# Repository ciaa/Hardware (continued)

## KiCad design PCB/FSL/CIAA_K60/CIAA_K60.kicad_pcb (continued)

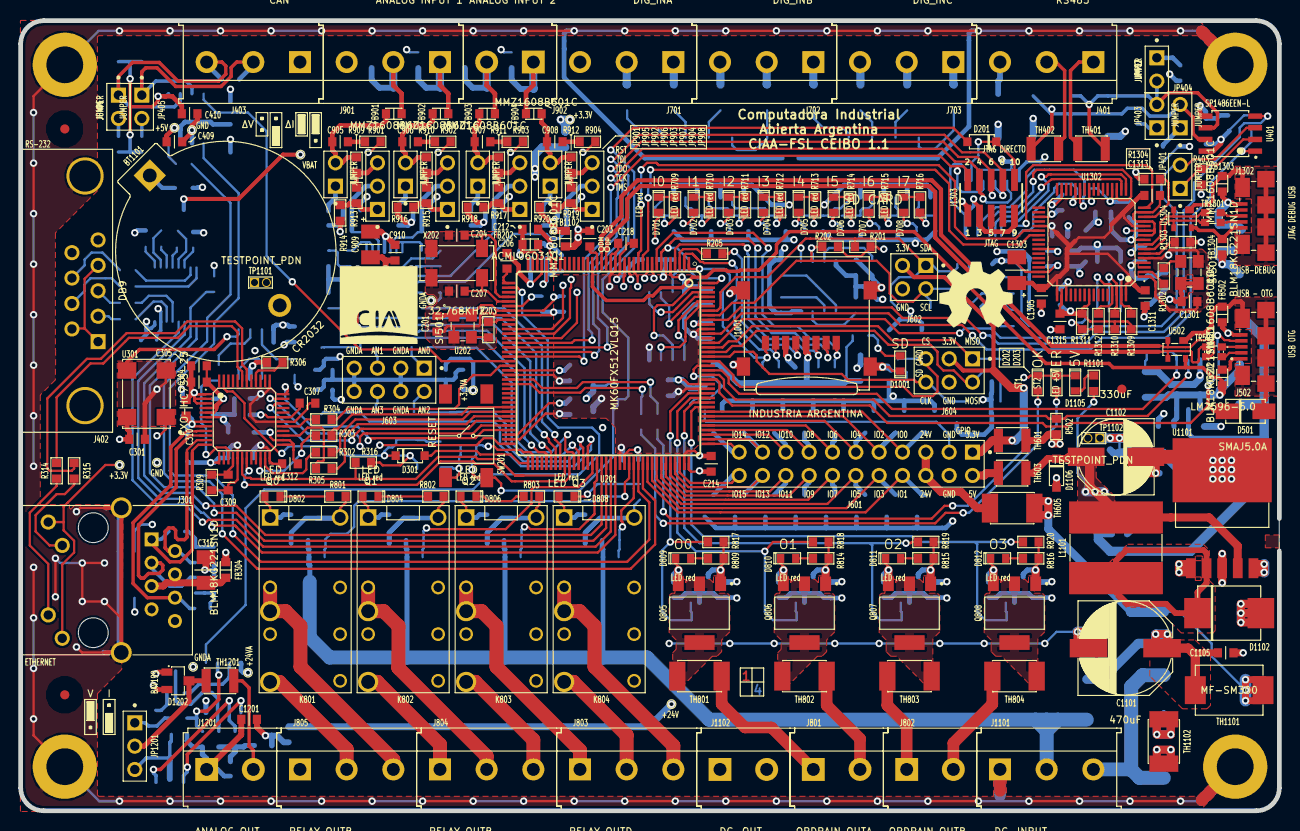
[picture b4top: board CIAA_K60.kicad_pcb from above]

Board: 4 copper layers, 137.0 x 86.0 mm, 467 parts (0 on the bottom side), 326 nets.

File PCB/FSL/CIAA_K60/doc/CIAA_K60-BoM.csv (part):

CIAA - PCB
10 sep 2014
CEIBO 1.0
CIAA - COMPUTADORA INDUSTRIAL ABIERTA ARGENTINA. Versión FSL Freescale K60
Autores: Ver 'doc/CHANGES.txt'      Licencia: Ver  'doc/LICENCIA_CIAA_FSL.txt'
Fecha de Generación: 19/09/2014-11:18:31

REF;VALUE;CANT;DESC;PN-DIGI-KEY;FAB;FOOT;DATA;URL
BT1101;CR2032;1;HOLDER BATTERY FOR 2032 CELL;BH32T-C-ND;MPD;2032batPTH;../datasheets/connectors/BH32T-C.pdf;http://search.digikey.com/scripts/DkSearch/dksus.dll?Detail&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
C201, C205, C206, C209, C210, C213, C214, C217, C218, C221, C223, C224, C227, C230, C302, C304, C305, C306, C307, C310, C312, C314, C315, C317, C402, C403, C404, C406, C407, C408, C409, C410, C501, C503, C801, C802, C803, C804, C910, C911, C912, C913, C914, C1001, C1002, C1003, C1005, C1104, C1106, C1201, C1301, C1302, C1305, C1306, C1307, C1311, C1312, C1313, C1314, C1315, C1316, C1317, C1318, C1319;100nF;64;CAP CER 0.1UF 16V 10% X7R 0603;399-1096-1-ND;Kemet;c_0603;../datasheets/passive/Capacitores/KEM_C1002_X7R_SMD.pdf;http://search.digikey.com/scripts/DkSearch/dksus.dll?Detail&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
C203;2.2uF;1;CAP CER 2.2UF 10V 10% X7R 0603;587-2983-1-ND;Taiyo Yuden;c_0603; ;http://search.digikey.com/scripts/DkSearch/dksus.dll?Detail&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
C204, C207;18pF;2;CAP CER 18PF 50V 5% NP0 0603;399-1052-1-ND;Kemet;c_0603; ;http://search.digikey.com/scripts/DkSearch/dksus.dll?Detail&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
C208, C212, C301, C1202;10nF;4;CAP CER 10000PF 50V 10% X7R 0603;399-1091-1-ND;Kemet;c_0603; ;http://search.digikey.com/scripts/DkSearch/dksus.dll?Detail&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
C231, C303, C401, C405, C909, C1004, C1103;10uF;7;CAP TANT 10UF 6.3V 10% 1206;399-10116-1-ND;Kemet;c_1206POL;../datasheets/passive/Capacitores/KEM_TC111_SPACE.pdf;http://search.digikey.com/scripts/DkSearch/dksus.dll?Detail&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
C308, C311, C313, C316;22uF;4;CAP TANT 22UF 6.3V 10% 1206;399-8279-1-ND;Kemet;c_1206POL; ;http://search.digikey.com/scripts/DkSearch/dksus.dll?Detail&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
C309;100pF;1;CAP CER 100PF 50V 10% X7R 0603;399-7824-1-ND;Kemet;c_0603; ;http://search.digikey.com/scripts/DkSearch/dksus.dll?Detail&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
C502, C1303, C1308, C1309, C1310;4,7uF;5;CAP TANT 4,7uF 6,3V 10% 1206 ;399-9717-1-ND;KEMET;c_1206POL; ;http://search.digikey.com/scripts/DkSearch/dksus.dll?Detail&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
C701, C702, C703, C704, C705, C706, C707, C708;1,5nF;8;CAP CER 1500PF 50V 10% X7R 0603;399-1084-1-ND;Kemet;c_0603; ;http://search.digikey.com/scripts/DkSearch/dksus.dll?Detail&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
C805, C806, C807, C808;1uF;4;CAP CER 1UF 16V 10% X7R 0603;399-7847-1-ND;Kemet;c_0603; ;http://search.digikey.com/scripts/DkSearch/dksus.dll?Detail&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
C901, C902, C903, C904;1nF;4;CAP CER 1000PF 50V 10% X7R 0603;399-1082-1-ND;Kemet;c_0603; ;http://search.digikey.com/scripts/DkSearch/dksus.dll?Detail&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
C905, C906, C907, C908;470pF;4;CAP CER 470PF 50V 10% X7R 0603;399-1075-1-ND;Kemet;c_0603; ;http://search.digikey.com/scripts/DkSearch/dksus.dll?Detail&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
C1101;470uF;1;CAP ALUM 470UF 35V 20% SMD;493-3961-1-ND;Nichicon;c_elec_10x13_5; ;http://search.digikey.com/scripts/DkSearch/dksus.dll?Detail&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
C1102;330uF;1;CAP ALUM 330UF 25V 20% SMD;493-9422-1-ND;Nichicon;c_elec_8x10; ;http://search.digikey.com/scripts/DkSearch/dksus.dll?Detail&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
C1105;100nF;1;CAP CER 0.1UF 50V 10% X7R 0603;1276-1936-1-ND;Samsung;c_0603; ;http://search.digikey.com/scripts/DkSearch/dksus.dll?Detail&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
D201, D301, D302, D801, D803, D805, D807;LL4148;7;DIODE SMALL SIG 100V 0.2A SOD80;LL4148FSCT-ND;Fairchild;SOD-123;../datasheets/passive/diode/LL4148.pdf;http://search.digikey.com/scripts/DkSearch/dksus.dll?Detail&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
D202, D1001;ST1, SD CARD;2;LED GRN WATER CLEAR 0603 SMD;1080-1399-1-ND;Everlight Electronics Co Ltd;LED-0603;../datasheets/passive/diode/ds300084.pdf;http://search.digikey.com/scripts/DkSearch/dksus.dll?Detail&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
D203, D701, D702, D703, D704, D705, D706, D707, D708, D802, D804, D806, D808, D809, D810, D811, D812, D1105;ST2, LED red, LED +5V;18;LED ALG RED WTR CLR 0603 SMD;1080-1400-1-ND;Everlight Electronics Co Ltd;LED-0603;../datasheets/passive/ds300084.pdf;http://search.digikey.com/scripts/DkSearch/dksus.dll?Detail&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
D401, D402, D403;P6SMB12CAT3G;3;TVS DIODE 10.2VWM 16.7VC SMB;P6SMB12CAT3GOSCT-ND;ON Semiconductor;DO-214AA_SMB;../datasheet/passive/diode/psd12c.pdf;http://search.digikey.com/scripts/DkSearch/dksus.dll?Detail&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
D404;PESD1CAN;1;TVS DIODE 24VWM 70VC SOT23;568-4032-1-ND;NXP Semiconductors;SOT-23;../datasheet/passive/diode/PESD1CAN.pdf;http://search.digikey.com/scripts/DkSearch/dksus.dll?Detail&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
D501;SMAJ5.0A;1;TVS DIODE 5VWM SMD;SMAJ5.0ABCT-ND;Bourns Inc.;DO-214AC_SMA;../datasheets/passive/protect/SMAJ.pdf;http://search.digikey.com/scripts/DkSearch/dksus.dll?Detail&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
D601, D602, D603, D604, D605, D606, D607, D609, D611, D612, D614, D615, D616, D617, D618, D619, D620, D621, D622, D624, D626, D627, D629, D630, D631, D632, D901, D902, D903, D904, D1201, D1202;BAV199;32;DIODE ARRAY 70V 215MA SOT23;BAV199LT1GOSCT-ND;ON Semiconductor;SOT-23;../datasheets/passive/protect/BAV199LT1-D.PDF;http://search.digikey.com/scripts/DkSearch/dksus.dll?Detail&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
D905, D906, D907, D908;P6SMB20CAT3G;4;TVS DIODE 17.1VWM 27.7VC SMB;P6SMB20CAT3GOSCT-ND;ON Semiconductor;DO-214AA_SMB;../ datasheets/passive/protect/P6SMB_Series.pdf;http://search.digikey.com/scripts/DkSearch/dksus.dll?Detail&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
D1101, D1109;MURS360;2;DIODE ULTRAFAST 600V 3A SMC;MURS360T3GOSCT-ND;ON Semiconductor;DO-214AB_SMC;../datasheet/passive/diode/MURS320T3-D.pdf;http://search.digikey.com/scripts/DkSearch/dksus.dll?Detail&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
D1102;MBRS540T3G;1;DIODE SCHOTTKY 40V 5A SMC;MBRS540T3GOSCT-ND;ON Semiconductor;DO-214AB_SMC;../datasheets/passive/diode/MBRS540T3-D.pdf;http://search.digikey.com/scripts/DkSearch/dksus.dll?Detail&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
D1103, D1104;MBRS130LT3G;2;DIODE SCHOTTKY 30V 2A SMB;MBRS130LT3GOSCT-ND;ON Semiconductor;DO-214AA_SMB;../datasheets/passive/diode/MBRS130LT3-D.pdf;http://search.digikey.com/scripts/DkSearch/dksus.dll?Detail&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
D1106;MMSZ5V6T1G;1;DIODE ZENER 5.6V 500MW SOD123;MMSZ5V6T1GOSCT-ND;ON Semiconductor;SOD-123;../datasheets/passive/diode/MMSZ2V4T1-D.pdf;http://search.digikey.com/scripts/DkSearch/dksus.dll?Detail&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
D1107;P6SMB33CA;1;TVS DIODE 28.2VWM 45.7VC SMB;P6SMB33CA-E3/52GICT-ND;Vishay Semiconductor Diodes Division;DO-214AA_SMB;../datasheets/passive/protect/P6SMB_Series.pdf;http://search.digikey.com/scripts/DkSearch/dksus.dll?Detail&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
D1108;BAT54C;1;DIODE SCHOTTKY 30V 200MA;BAT54FSCT-ND;Fairchild Semiconductor;SOT-23; ;http://search.digikey.com/scripts/DkSearch/dksus.dll?Detail&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
FB201, FB202;ACML0603101;2;FERRITE CHIP 100 OHM 200MA 0603;ACML-0603-101-TCT-ND;Abracon Corporation;fb_0603;../datasheets/passive/Ferrite/ACML-0603.pdf;http://search.digikey.com/scripts/DkSearch/dksus.dll?Detail&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
FB301, FB302, FB303, FB304;BK1608HS220-T;4;Ferrite Bead 22OHM 1500mA;Alternativo: MH1608-221YCT-ND;Taiyo Yuden;fb_0603;../datasheets/passive/Ferrite/BK1608HS220-T.pdf;http://search.digikey.com/scripts/DkSearch/dksus.dll?Detail&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 MH1608-221YCT-ND
FB402, FB403, FB404, FB405;BLM18BD470SN1;4;FERRITE CHIP 47 OHM 500MA 0603;490-5211-1-ND;Murata Electronics North America;fb_0603;../datasheet/passive/Ferrite/L0110S0100BLM18B.pdf;http://search.digikey.com/scripts/DkSearch/dksus.dll?Detail&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
FB501;BLM18KG221SN1D;1;FERRITE CHIP 220 OHM 2200MA 0603;490-5255-1-ND;MURATA;fb_0603;../datasheets/passive/Ferrite/L0110S0100BLM18K.pdf;http://search.digikey.com/scripts/DkSearch/dksus.dll?Detail&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
FB502, FB901, FB902, FB903, FB904, FB1101, FB1102, FB1201, FB1301, FB1302;MMZ1608B601C;10;FERRITE CHIP 600 OHM 500MA 0603;445-2166-1-ND;TDK Corporation;fb_0603;../datasheets/passive/Ferrite/E9412_MMZ.pdf;http://search.digikey.com/scripts/DkSearch/dksus.dll?Detail&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
FB1303, FB1304;BLM18BD331SN1D;2;FERRITE CHIP 330 OHM 200mA 0603;490-5251-1-ND;MURATA;fb_0603;../datasheets/passive/Ferrite/L0110S0100BLM18B.pdf;http://search.digikey.com/scripts/DkSearch/dksus.dll?Detail&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
J301;ETHERNET;1;CONN MAGJACK 1PORT 100 BASE-TX;553-1483-ND;Pulse;RJ45_Pulse_J403-A;../datasheets/connectors/J0011D01BNL.pdf;http://search.digikey.com/scripts/DkSearch/dksus.dll?Detail&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

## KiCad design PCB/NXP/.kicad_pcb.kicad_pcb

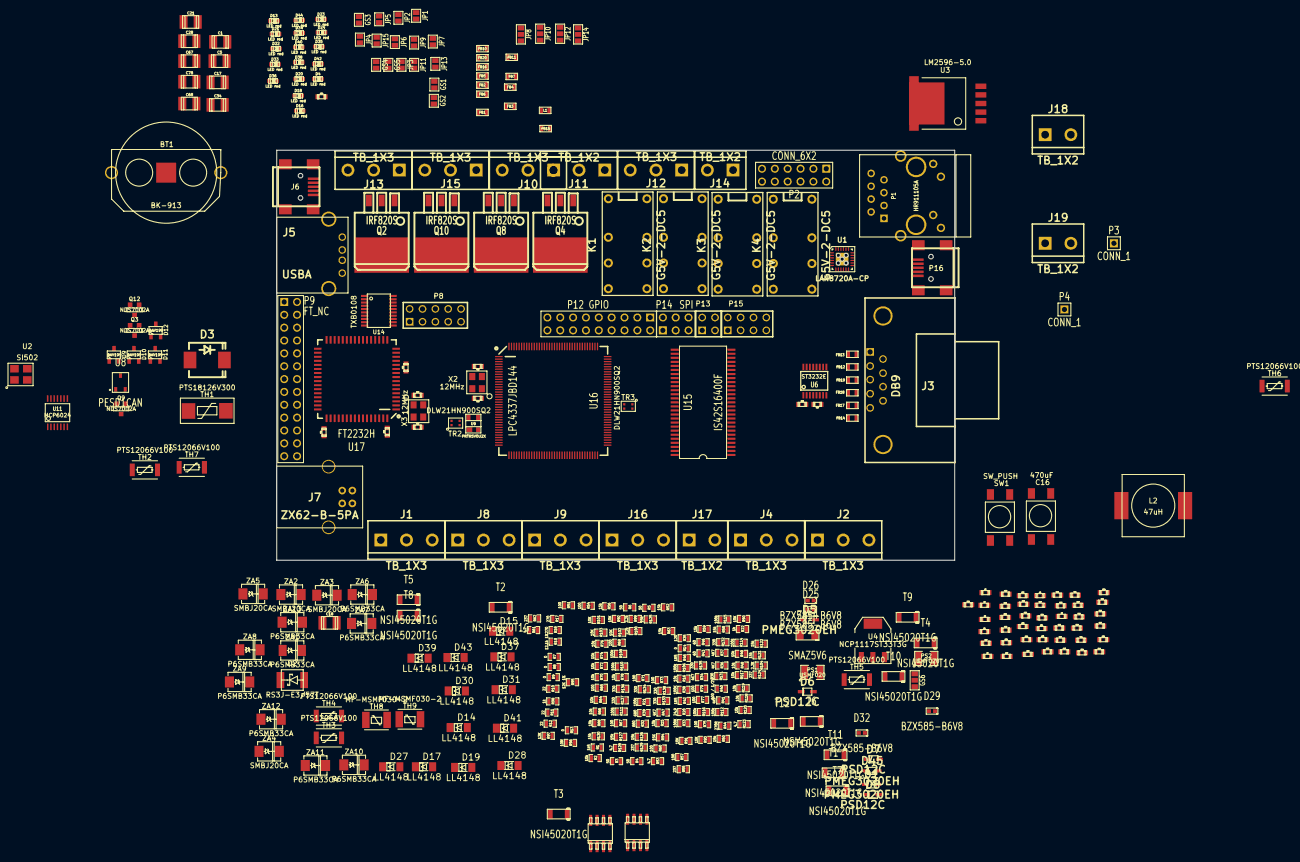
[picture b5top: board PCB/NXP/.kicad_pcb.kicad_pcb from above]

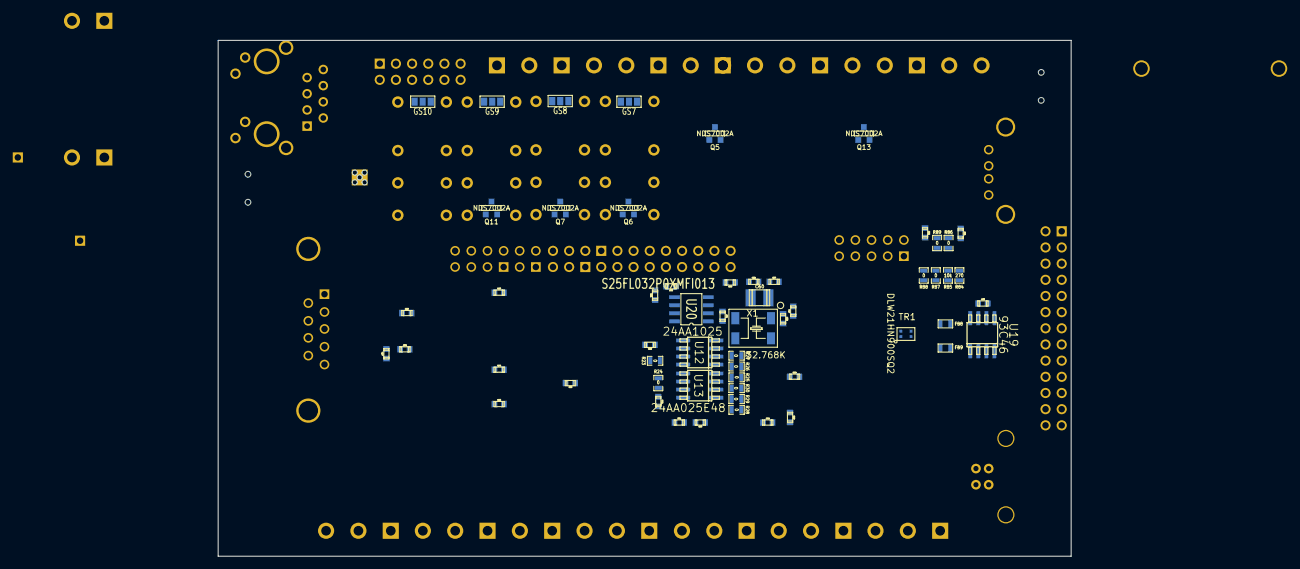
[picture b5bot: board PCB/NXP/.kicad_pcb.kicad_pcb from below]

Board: 4 copper layers, 134.0 x 81.0 mm, 420 parts (57 on the bottom side), 374 nets, no tracks yet.

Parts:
BT1: BK-913; BK-913-ND
C1, C5, C18, C34, C60, C68, C78: 10uF; c_1210
C2, C3, C4, C6, C7, C8, C9, C10, C15, C19, C20, C22, C23, C24, C25, C26, C27, C29, C30, C32, C33, C35, C37, C39, C41, C43, C45, C47, C48, C49, C50, C51, C52, C53, C54, C55, C56, C57, C58, C59, C61, C62, C63, C64, C65, C66, C69, C70, C71, C72, C73, C74, C75, C76, C77, C86, C87, C90: 100nF; c_0603
C11, C12, C13, C14: 18pF; c_0603
C16: 470uF; PUSH_SWITCH
C17: 330uF; c_1210
C21, C28: 10uF / 6V3; c_1210
C31: 10uF; c_0603
C36, C42, C91, C93: 1nF; c_0603
C38, C40, C44, C92: 470pF; c_0603
C67: 100nF; c_1210
C79, C81: 15p; c_0603
C80: 3.3uF; c_0603
C82, C83: 20p; c_0603
C84, C85: 22p; c_0603
D1, D5, D45: PMEG3020EH; SOD323
D2: RS3J-E3/57T; DO-214AB(SMC)
D3: B540C-13-F; Diode-SMC_Standard_RevA_26July2010
D4, D13, D16, D18, D20, D21, D22, D23, D24, D33, D34, D35, D36, D38, D40, D42, D44: LED red; LED-0603
D6, D7, D8: PSD12C; SOD323
D9, D10, D11, D12: BAV199; SOT23-DIODE
D14, D15, D17, D19, D27, D28, D30, D31, D37, D39, D41, D43: LL4148; MiniMelf
D25, D26, D29, D32: BZX585-B6V8; SOD523
FB1, FB2, FB3, FB4, FB5, FB6, FB8, FB9, FB10, FB20: MMZ1608B601C; SM0603
FB7, FB11, FB14, FB15, FB16: BLM18KG221SN1; SM0603
FB12, FB13, FB17, FB18, FB19: BLM18BD470SN1; SM0603
GS1, GS2, GS3, GS4, GS5: GS2
GS6, GS7, GS8, GS9, GS10: GS3
J1, J2, J4, J8, J9, J10, J12, J13, J15, J16: TB_1X3; bornier3
J3: DB9; DB9FC
J5: USBA; USB_A
J6: ZX62-AB-5PA; USB_MINI_B
J7: ZX62-B-5PA; USB_B
J11: TB_1X2; bornier3
J14, J17, J18, J19: TB_1X2; bornier2
JP1, JP2, JP3, JP4, JP5, JP6: JUMPER-2; GS2
JP7, JP9, JP11, JP13: JUMPER; GS2
JP8, JP10, JP12, JP14: JUMPER3; GS3
JP15: ISP; GS2
K1, K2, K3, K4: G5V-2-DC5; G5V-2
L1: BK1608HS220-T; SM0603
L2: 47uH; SMT power inductors
P1: HR911105A; RJ45_Pulse_J403-A
P2: CONN_6X2; PIN_ARRAY_6X2
P3, P4: CONN_1; PIN_ARRAY_1X1
P8: Cortex-Debug; PIN_ARRAY_5x2
P9: FT_NC; PIN_ARRAY_13X2
P12: GPIO; PIN_ARRAY_9X2
P13: I2C; PIN_ARRAY_2X2
P14: SPI; PIN_ARRAY_3X2
P15: Analog; pin_array_4x2
P16: ZX62-B-5PA; USB_MINI_B
PS1, PS2: USMF020; SM1210
Q2, Q4, Q8, Q10: IRF820S; TO263
Q3, Q5, Q6, Q7, Q9, Q11, Q12, Q13: NDS7002A; SOT23GDS
R1: 1k5; SM0603_Resistor
R2, R15, R16, R48, R49, R64, R66, R68, R70, R72, R74, R76, R78, R85, R117, R118, R119, R120: 10k; SM0603_Resistor
R3, R4, R5, R6: 50; SM0603_Resistor
R7, R8, R9, R13, R14, R23, R24, R25, R26, R27, R28, R29, R30, R86, R87, R88, R89: 0; SM0603_Resistor
R10, R11, R12: 22; SM0603_Resistor
R17, R18, R84: 270; SM0603_Resistor
R19: 12.1k 1%; SM0603_Resistor
R20: 24.9; SM0603_Resistor
R21, R106, R108, R110, R111, R112, R114, R115, R116: 100k; SM0603_Resistor
R22, R98: 1k; SM0603_Resistor
R32, R39: 680; SM0603_Resistor
R33, R38: 100K; SM0603_Resistor
R34, R36, R37, R41, R47: 4K7; SM0603_Resistor
R35: 120; SM0603_Resistor
R40: 100 / 1/2W; SM0603_Resistor
R42, R45: 1K5; SM0603_Resistor
R43, R46: 60; SM0603_Resistor
R44: 270R; SM0603_Resistor
R50, R52, R56, R58, R59, R63, R121, R122, R125, R126, R127, R130: 15k; SM0603_Resistor
R51, R54, R57, R60, R65, R67, R69, R71, R73, R75, R77, R79: 100; SM0603_Resistor
R53, R61, R123, R128: 4.7; SM0603_Resistor
R55, R62, R124, R129: 237; SM0603_Resistor
R90, R91, R92, R101, R102, R103: 10K; SM0603_Resistor
R93, R94: 15K; SM0603_Resistor
R95: 12K 1%; SM0603_Resistor
R96: 10M; SM0603_Resistor
R97: 12K; SM0603_Resistor
R99, R100: 2.2k; SM0603_Resistor
R104: 2.2K; SM0603_Resistor
R131, R132, R133, R134, R135, R136, R137, R138: 330; SM0603_Resistor
SW1: SW_PUSH; PUSH_SWITCH
T1, T2, T3, T4, T5, T6, T7, T8, T9, T10, T11, T12: NSI45020T1G; SOD123
TH1: PTS18126V300; MF-SM030
TH2, TH3, TH4, TH5, TH6, TH7: PTS12066V100; MF-USMF
TH8, TH9: MF-MSMF030-2; MF-MSMF
TR1, TR2, TR3: DLW21HN900SQ2; SRF2012
U1: LAN8720A-CP; QFN24
U2: SI502; 4SMD
U3: LM2596-5.0; D2PACK5-LM2596
U4: NCP1117ST33T3G; SOT223
U6: ST3232E; TSSOP16
U7: TJA1040; -SOIC8
U8: PESD1CAN; SOT23-3
U9: PRTR5V0U2X; sot143B
U10: MIC2025-2YM; -SOIC8
U11: MCP6024; TSSOP14
U12: 24AA1025; -SOIC8
U13: 24AA025E48; -SOIC8
U14: TXB0108; tssop-20
U15: IS42S16400F; TSOP54-M08-T2
U16: LPC4337JBD144; LQFP144-M05
U17: FT2232H; LQFP64-M08
U19: 93C46; -SOIC8
U20: S25FL032P0XMFI013; SO8
X1: 32.768K; 4SOJ
X2, X3: 12MHz; FA238V-XTAL
ZA1: P6SMB33CA; DO-214AC(SMA)
ZA2, ZA3, ZA4, ZA5: SMBJ20CA; DO-214AA(SMB)
ZA6, ZA7, ZA8, ZA9, ZA10, ZA11, ZA12, ZA13: P6SMB33CA; DO-214AA(SMB)
ZA14: SMAZ5V6; SOD123F

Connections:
+3.3V: C4.1, C5.1, C6.1, C15.1, C18.1, C19.1, C20.1, C21.2, C22.1, C23.1, C45.1, C47.2, C48.2, C49.2, C50.2, C51.2, C52.2, C53.2, C54.2, C55.2, C56.2, C57.2, C58.2, C61.2, C62.2, C63.1, C64.1, C65.1, C66.1, C73.1, C74.1, C75.1, C76.1, C90.1, D8.1, FB6.1, FB8.2, FB9.2, L1.1, P8.1, R1.1, R2.1, R15.1, R16.1, R18.1, R21.2, R27.1, R28.1, R32.1, R33.1, R34.1, R49.1, R64.2, R66.2, R68.2, R70.2, R72.2, R74.2, R76.2, R78.2, R90.2, R91.2, R92.2, R98.1, R99.1, R100.1, R101.1, R102.1, R103.1, R106.1, R108.1, R110.1, R114.1, TH8.1, U1.9, U2.4, U4.2, U6.16, U12.8, U13.8, U14.2, U14.19, U15.1, U15.3, U15.9, U15.14, U15.27, U15.43, U15.49, U16.5, U16.25, U16.36, U16.41, U16.59, U16.71, U16.77, U16.94, U16.107, U16.111, U16.131, U16.141, U17.20, U17.31, U17.42, U17.50, U17.56, U19.6, U19.8, U20.8
+3.3VADC: C34.1, C35.1, C59.1, C60.1, C86.1, C87.1, D9.3, D10.3, D11.3, D12.3, FB6.2, U11.4, U16.16, U16.17, U16.137
+5V: C17.1, C28.2, C29.2, C33.1, D1.2, D5.2, D27.2, D28.2, D30.2, D31.2, D45.2, K1.8, K2.8, K3.8, K4.8, L2.2, R22.1, R133.2, R134.2, R136.2, R137.2, TH9.2, U3.4, U4.3, U7.3, U10.7, ZA14.1
+24V: D2.2, T9.2, T10.2, T11.2, T12.2, TH1.1, TH2.1, TH3.2
/CPU/AIN0: C37.1, R51.2, U16.2
/CPU/AIN1: C39.1, R54.2, U16.143
/CPU/AIN2: C41.1, R57.2, U16.139
/CPU/AIN3: C43.1, R60.2, U16.138
/CPU/AUX_CLK: P12.14, U16.99
/CPU/CAN_RD: R44.1, U16.114
/CPU/CAN_TD: U7.1, U16.116
/CPU/DIN0: R64.1, U16.1
/CPU/DIN1: R66.1, U16.3
/CPU/DIN2: R68.1, U16.8
/CPU/DIN3: R70.1, U16.7
/CPU/DIN4: R72.1, U16.117
/CPU/DIN5: R74.1, U16.132
/CPU/DIN6: R76.1, U16.133
/CPU/DIN7: R78.1, U16.134
/CPU/DOUT0: Q6.G, R111.1, U16.9
/CPU/DOUT1: Q7.G, R112.1, U16.10
/CPU/DOUT2: Q11.G, R115.1, U16.11
/CPU/DOUT3: Q12.G, R116.1, U16.81
/CPU/DOUT4: Q3.G, R106.2, U16.15
/CPU/DOUT5: Q5.G, R108.2, U16.33
/CPU/DOUT6: Q9.G, R110.2, U16.35
/CPU/DOUT7: Q13.G, R114.2, U16.48
/CPU/EECLK: R102.2, U17.62, U19.2
/CPU/EECS: R103.2, U17.63, U19.1
/CPU/EEDATA: R104.1, U17.61, U19.3
/CPU/EMA_A1: U15.24, U16.104
/CPU/EMA_A2: U15.25, U16.105
/CPU/EMA_A6: U15.31, U16.42
/CPU/EMC_A0: U15.23, U16.102
/CPU/EMC_A3: U15.26, U16.106
/CPU/EMC_A4: U15.29, U16.108
/CPU/EMC_A5: U15.30, U16.38
/CPU/EMC_A7: U15.32, U16.43
/CPU/EMC_A8: U15.33, U16.98
/CPU/EMC_A9: JP15.2, U15.34, U16.96
/CPU/EMC_A10: U15.22, U16.95
/CPU/EMC_A11: U15.35, U16.84
/CPU/EMC_A13: U15.20, U16.75
/CPU/EMC_A14: U15.21, U16.86
/CPU/EMC_CAS: U15.17, U16.80
/CPU/EMC_CKE: U15.37, U16.101
/CPU/EMC_CLK0: U15.38, U16.45
/CPU/EMC_D0: U15.2, U16.50
/CPU/EMC_D1: U15.4, U16.51
/CPU/EMC_D2: U15.5, U16.52
/CPU/EMC_D3: U15.7, U16.53
/CPU/EMC_D4: U15.8, U16.55
/CPU/EMC_D5: U15.10, U16.56
/CPU/EMC_D6: U15.11, U16.60
/CPU/EMC_D7: U15.13, U16.61
/CPU/EMC_D8: U15.42, U16.57
/CPU/EMC_D9: U15.44, U16.58
/CPU/EMC_D10: U15.45, U16.63
/CPU/EMC_D11: U15.47, U16.65
/CPU/EMC_D12: U15.48, U16.37
/CPU/EMC_D13: U15.50, U16.39
/CPU/EMC_D14: U15.51, U16.46
/CPU/EMC_D15: U15.53, U16.54
/CPU/EMC_DYCS: U15.19, U16.97
/CPU/EMC_LDQM: U15.15, U16.103
/CPU/EMC_RAS: U15.18, U16.82
/CPU/EMC_UDQM: U15.39, U16.100
/CPU/EMC_WE: U15.16, U16.49
/CPU/ENET_CRS_DV: R12.1, U16.64
/CPU/ENET_MDC: R14.1, U16.140
/CPU/ENET_MDIO: R13.1, U16.66
/CPU/ENET_REF_CLK: R20.2, U1.5, U16.68
/CPU/ENET_RXD0: R10.1, U16.62
/CPU/ENET_RXD1: R11.1, U16.32
/CPU/ENET_TXD0: R7.1, U16.67
/CPU/ENET_TXD1: R8.1, U16.70
/CPU/ENET_TX_EN: R9.1, U16.34
/CPU/FT_OE: R84.2, U17.28
/CPU/FT_RST: U14.7, U17.27
/CPU/FT_TCK: U14.1, U17.16
/CPU/FT_TDI: U14.3, U17.17
/CPU/FT_TDO: U14.4, U17.18
/CPU/FT_TMS: U14.5, U17.19
/CPU/FT_TRST: U14.6, U17.26
/CPU/FT_XTIN: C84.2, U17.2, X3.2
/CPU/FT_XTOUT: C85.2, U17.3, X3.1
/CPU/GPIO0: GS6.3, P12.5, U16.74
/CPU/GPIO1: GS1.1, P12.6, U16.91
/CPU/GPIO2: GS2.1, P12.7, U16.110
/CPU/GPIO3: GS3.1, P12.8, P14.5, U16.85
/CPU/I2C_SCL: P13.2, R99.2, U12.6, U13.6, U16.92
/CPU/I2C_SDA: P13.1, R100.2, U12.5, U13.5, U16.93
/CPU/RS232_RXD: U6.12, U16.88
/CPU/RS232_TXD: U6.11, U16.87
/CPU/RS485_DIR: JP3.1, R37.1, U16.78
/CPU/RS485_TXD: R34.2, U16.69
/CPU/RTCX1: C81.2, U16.125, X1.2
/CPU/RTCX2: C79.2, U16.126, X1.1
/CPU/SPIFI_CS: U16.124, U20.1
/CPU/SPIFI_IO2: U16.121, U20.3
/CPU/SPIFI_IO3: U16.119, U20.7
/CPU/SPIFI_MISO: U16.122, U20.2
/CPU/SPIFI_MOSI: U16.123, U20.5
/CPU/SPI_MISO: P14.1, U16.44
/CPU/SPI_MOSI: P14.2, U16.47
/CPU/SPI_SCK: P14.6, U16.120
/CPU/TCK: P8.4, U14.20, U16.27
/CPU/TDI: P8.8, U14.18, U16.26
/CPU/TDO: P8.6, U14.17, U16.31
/CPU/TMS: P8.2, U14.16, U16.30
/CPU/U2_RXD: U16.115, U17.38
/CPU/U2_TXD: U16.113, U17.39
/CPU/USB_AUX_DM: TR3.3, U16.90
/CPU/USB_AUX_DP: TR3.2, U16.89
/CPU/USB_DEBUG_VBUS: D1.1, FB11.1
/CPU/USB_DM: R94.1, TR2.2, U9.2, U16.20
/CPU/USB_DP: R93.1, TR2.3, U9.3, U16.18
/CPU/USB_ID: J6.4, U16.22
/CPU/USB_JTAG_1.8V: C70.1, C71.1, C72.1, C80.1, U17.12, U17.37, U17.49, U17.64
/CPU/USB_JTAG_DM: TR1.2, U17.7
/CPU/USB_JTAG_DP: TR1.3, U17.8
/CPU/USB_VBUS: C31.1, C32.1, D5.1, FB15.2, U9.4, U10.6, U10.8, U16.21
/CPU/XTAL1: C82.2, R96.2, U16.12, X2.2
/CPU/XTAL2: C83.2, R96.1, U16.13, X2.1
/CPU/nTRST: R92.1, U16.29
/Entradas Digitales/COM: J9.3, ZA6.1, ZA7.1, ZA8.1, ZA9.1, ZA10.1, ZA11.1, ZA12.1, ZA13.1
/Entradas Digitales/IN0: J1.1, R65.1
/Entradas Digitales/IN1: J1.2, R67.1
/Entradas Digitales/IN2: J1.3, R69.1
/Entradas Digitales/IN3: J8.1, R71.1
/Entradas Digitales/IN4: J8.2, R73.1
/Entradas Digitales/IN5: J8.3, R75.1
/Entradas Digitales/IN6: J9.1, R77.1
/Entradas Digitales/IN7: J9.2, R79.1
/Ethernet/LED_100M: P1.11, R16.2, U1.2
/Ethernet/LED_LINK: P1.9, U1.3
/Ethernet/PHY_nRESET: GS6.2, U1.15
/GPIO/AN0: R117.1, U16.6
/GPIO/AN1: R119.1, U16.144
/GPIO/AN2: R118.1, U16.142
/GPIO/AN3: R120.1, U16.136
/GPIO/GPIO4: P12.9, U16.73
/GPIO/GPIO5: P12.10, U16.112
/GPIO/GPIO6: P12.11, U16.14
/GPIO/GPIO7: GS4.1, P12.12, U16.79
/GPIO/GPIO8: GS5.1, P12.13, U16.83
/GPIO/GPIO10: P12.15, U16.129
/GPIO/GPIO11: P12.16, U16.130
/GPIO/GPIO12: C69.1, GS6.1, P8.10, P12.17, R90.1, SW1.2, U16.128
/GPIO/USB_VBUS: D45.1, FB16.2
/GPIO/USR_3.3V: P12.1, P13.3, P14.3, TH8.2
/GPIO/USR_5V: P12.2, TH9.1
/Memorias NV/SPIFI_CLK: U16.118, U20.6
/RS485_RS232_CAN/CAN_H: J4.1, R42.2, R43.1, U7.7, U8.2
/RS485_RS232_CAN/CAN_L: J4.2, R45.1, R46.1, U7.6, U8.1
/RS485_RS232_CAN/CAN_STB: GS1.2, R47.2, U7.8
/RS485_RS232_CAN/RS232_CTS: GS3.2, U6.9
/RS485_RS232_CAN/RS232_RTS: GS2.2, R41.1, U6.10
/Salidas Digitales/NO1A: GS7.3, K1.16
/Salidas Digitales/NO1B: K1.1, P2.5
/Salidas Digitales/NO2A: GS8.3, K2.16
/Salidas Digitales/NO2B: K2.1, P2.11
/Salidas Digitales/NO3A: GS9.3, K3.16
/Salidas Digitales/NO3B: K3.1, P2.6
/Salidas Digitales/NO4A: GS10.3, K4.16
/Salidas Digitales/NO4B: K4.1, P2.12
/USB OTG/USB0_PPWR: GS4.2, R48.2, U10.1
/USB OTG/USB0_PWR_FAULT: GS5.2, R49.2, U10.2
GND: BT1.2, C1.2, C2.2, C3.2, C4.2, C5.2, C6.2, C7.2, C8.2, C9.2, C10.2, C11.2, C12.2, C13.2, C14.2, C15.2, C16.2, C17.2, C18.2, C19.2, C20.2, C21.1, C22.2, C23.2, C25.2, C27.2, C28.1, C29.1, C30.2, C31.2, C32.2, C33.2, C45.2, C47.1, C48.1, C49.1, C50.1, C51.1, C52.1, C53.1, C54.1, C55.1, C56.1, C57.1, C58.1, C61.1, C62.1, C63.2, C64.2, C65.2, C66.2, C67.2, C68.2, C69.2, C70.2, C71.2, C72.2, C73.2, C74.2, C75.2, C76.2, C77.2, C78.2, C79.1, C80.2, C81.1, C82.1, C83.1, C84.1, C85.1, C90.2, D3.1, D4.2, D7.2, D21.2, D22.2, D25.1, D26.1, D29.1, D32.1, D33.2, D36.2, FB1.1, FB7.2, FB10.1, FB14.2, FB20.1, J4.3, J5.4, J6.5, J14.2, J15.3, J18.2, JP15.1, P1.8, P1.13, P8.3, P8.5, P8.9, P12.3, P12.4, P13.4, P14.4, P16.4, P16.5, Q2.3, Q3.S, Q4.3, Q5.S, Q6.S, Q7.S, Q8.3, Q9.S, Q10.3, Q11.S, Q12.S, Q13.S, R17.1, R19.2, R23.2, R24.2, R25.1, R26.1, R29.1, R30.1, R36.2, R37.2, R38.2, R39.2, R40.1, R41.2, R47.1, R48.1, R85.2, R86.1, R87.1, R88.1, R89.1, R93.2, R94.2, R95.2, R97.1, R111.2, R112.2, R115.2, R116.2, SW1.1, U2.2, U3.3, U3.5, U4.1, U6.15, U7.2, U8.3, U9.1, U10.3, U12.4, U13.4, U14.11, U15.6, U15.12, U15.28, U15.41, U15.46, U15.52, U15.54, U16.4, U16.40, U16.76, U16.109, U17.1, U17.5, U17.10, U17.11, U17.13, U17.15, U17.25, U17.35, U17.47, U17.51, U19.5, U19.7, U20.4, X1.3, ZA1.2, ZA14.2
GNDA: C34.2, C35.2, C36.2, C37.2, C39.2, C41.2, C42.2, C43.2, C59.2, C60.2, C86.2, C87.2, C91.2, C93.2, D9.1, D10.1, D11.1, D12.1, FB20.2, J17.2, P15.3, P15.4, P15.7, P15.8, R53.1, R55.1, R56.1, R61.1, R62.1, R63.1, R123.1, R124.1, R125.1, R128.1, R129.1, R130.1, U11.11, U16.19, U16.23, U16.135, ZA2.1, ZA3.1, ZA4.1, ZA5.1
unnamed: R86.2, U14.8
unnamed: R87.2, U14.9
unnamed: R89.2, U14.13
unnamed: R88.2, U14.12
unnamed: R97.2, U17.6
unnamed: C77.1, C78.1, FB9.1, U17.4
unnamed: R84.1, R85.1, U14.10
unnamed: P9.17, U17.48
unnamed: P9.7, U17.41
unnamed: P9.5, U17.40
unnamed: P9.11, U17.44
unnamed: R98.2, U17.14
unnamed: P9.9, U17.43
unnamed: P9.1, U17.33
unnamed: J7.3, TR1.4
unnamed: J7.2, TR1.1
unnamed: R101.2, R104.2, U19.4
unnamed: P9.8, U17.24
unnamed: P9.14, U17.21
unnamed: P9.12, U17.22
unnamed: P9.10, U17.23
unnamed: P9.16, U17.36
unnamed: P9.6, U17.29
unnamed: P9.4, U17.30
unnamed: P9.2, U17.32
unnamed: C67.1, C68.1, FB8.1, U17.9
unnamed: FB11.2, J7.1
unnamed: BT1.1, U16.127
unnamed: FB7.1, J7.4, J7.5, J7.6
unnamed: P9.19, U17.52
unnamed: P9.20, U17.58
unnamed: P9.22, U17.59
unnamed: P9.24, U17.60
unnamed: P9.18, U17.57
unnamed: P9.25, U17.55
unnamed: P9.15, U17.46
unnamed: P9.23, U17.54
unnamed: P9.13, U17.45
unnamed: P9.3, U17.34
unnamed: P9.21, U17.53
unnamed: R91.1, U16.28
unnamed: R95.1, U16.24
unnamed: J2.1, PS1.2
unnamed: C26.1, U6.4
unnamed: C24.2, U6.3
unnamed: C24.1, U6.1
unnamed: J2.3, R40.2
unnamed: JP2.1, R35.1
unnamed: J2.2, PS2.2
unnamed: C26.2, U6.5
unnamed: D6.2, D7.1, JP4.2, PS2.1, R35.2, R38.1
unnamed: JP4.1, R39.1
unnamed: JP1.2, R32.2
unnamed: D6.1, D8.2, JP1.1, JP2.2, PS1.1, R33.2
unnamed: FB18.2, J3.8
unnamed: FB12.2, J3.7
unnamed: C27.1, U6.6
unnamed: FB13.2, J3.2
unnamed: FB19.2, J3.3
unnamed: JP5.1, R43.2
unnamed: JP6.1, R46.2
unnamed: FB14.1, J3.5
unnamed: C25.1, FB17.1, U6.2
unnamed: R44.2, U7.4
unnamed: FB13.1, U6.13
unnamed: FB18.1, U6.8
unnamed: FB12.1, U6.7
unnamed: FB19.1, U6.14
unnamed: FB17.2, J3.4
unnamed: C30.1, JP5.2, JP6.2, R42.1, R45.2, U7.5
unnamed: JP3.2, R36.1
unnamed: R29.2, U13.2
unnamed: R30.2, U13.3
unnamed: R28.2, U13.1
unnamed: R24.1, U13.7
unnamed: R27.2, U12.3
unnamed: R25.2, U12.1
unnamed: R26.2, U12.2
unnamed: R23.1, U12.7
unnamed: D2.1, J18.1
unnamed: C16.1, TH1.2, U3.1, ZA1.1
unnamed: D3.2, L2.1, U3.2
unnamed: D4.1, R22.2
unnamed: C13.1, P1.3, R5.2, U1.23
unnamed: R1.2, R13.2, U1.12
unnamed: C1.1, C2.1, C3.1, C9.1, C10.1, L1.2, P1.4, P1.5, R3.1, R4.1, R5.1, R6.1, U1.1, U1.19
unnamed: R2.2, U1.10
unnamed: C14.1, P1.6, R6.2, U1.22
unnamed: C12.1, P1.2, R4.2, U1.20
unnamed: C11.1, P1.1, R3.2, U1.21
unnamed: P1.12, R18.2
unnamed: C7.1, C8.1, U1.6
unnamed: R15.2, U1.14
unnamed: R21.1, U2.1
unnamed: R20.1, U2.3
unnamed: R19.1, U1.24
unnamed: P1.10, R17.2
unnamed: R14.2, U1.13
unnamed: R8.2, U1.18
unnamed: R9.2, U1.16
unnamed: R10.2, U1.8
unnamed: R11.2, U1.7
unnamed: R12.2, U1.11
unnamed: R7.2, U1.17
unnamed: FB1.2, J6.6, J6.7, J6.8, J6.9
unnamed: FB15.1, J5.1, J6.1
unnamed: J5.2, J6.3, TR2.4
unnamed: J5.3, J6.2, TR2.1
unnamed: JP9.1, R62.2
unnamed: JP10.3, R58.1, R59.2
unnamed: D10.2, JP10.2, U11.5
unnamed: JP10.1, R59.1, R63.2
unnamed: C40.1, FB3.2, JP9.2, R58.2
unnamed: JP8.1, R52.1, R56.2
unnamed: C42.1, FB3.1, J16.2, ZA3.2
unnamed: C40.2, R61.2
unnamed: C44.2, R123.2
unnamed: JP11.1, R124.2
unnamed: JP12.1, R122.1, R125.2
unnamed: JP12.3, R121.1, R122.2
unnamed: D11.2, JP12.2, U11.10
unnamed: R60.1, U11.13, U11.14
unnamed: R57.1, U11.8, U11.9
unnamed: C36.1, FB2.1, J16.1, ZA2.2
unnamed: R51.1, U11.1, U11.2
unnamed: R54.1, U11.6, U11.7
unnamed: D9.2, JP8.2, U11.3
unnamed: JP8.3, R50.1, R52.2
unnamed: JP7.1, R55.2
unnamed: C38.1, FB2.2, JP7.2, R50.2
unnamed: C38.2, R53.2
unnamed: C91.1, FB4.1, J16.3, ZA4.2
unnamed: C92.2, R128.2
unnamed: C44.1, FB4.2, JP11.2, R121.2
unnamed: C93.1, FB5.1, J17.1, ZA5.2
unnamed: JP13.1, R129.2
unnamed: D12.2, JP14.2, U11.12
unnamed: JP14.3, R126.1, R127.2
unnamed: C92.1, FB5.2, JP13.2, R126.2
unnamed: JP14.1, R127.1, R130.2
unnamed: P15.1, R117.2
unnamed: P15.5, R119.2
unnamed: P15.2, R118.2
unnamed: P16.2, TR3.1
unnamed: FB16.1, P16.1
unnamed: P15.6, R120.2
unnamed: J19.2, P4.1
unnamed: J19.1, P3.1
unnamed: P16.3, TR3.4
unnamed: FB10.2, P16.6, P16.7, P16.8, P16.9
unnamed: D19.1, R71.2, ZA9.2
unnamed: D19.2, T4.2
unnamed: D20.1, T4.1
unnamed: D37.1, R73.2, ZA10.2
unnamed: D38.1, T5.1
unnamed: D37.2, T5.2
unnamed: D16.1, T2.1
unnamed: D15.1, R67.2, ZA7.2
unnamed: D15.2, T2.2
unnamed: D14.2, T1.2
unnamed: D18.1, T3.1
unnamed: D17.1, R69.2, ZA8.2
unnamed: D17.2, T3.2
unnamed: D43.2, T8.2
unnamed: D44.1, T8.1
unnamed: D43.1, R79.2, ZA13.2
unnamed: D41.2, T7.2
unnamed: D42.1, T7.1
unnamed: D39.2, T6.2
unnamed: D40.1, T6.1
unnamed: D39.1, R75.2, ZA11.2
unnamed: D41.1, R77.2, ZA12.2
unnamed: D14.1, R65.2, ZA6.2
unnamed: D13.1, T1.1
unnamed: J13.3, TH5.2
unnamed: D26.2, Q4.2, Q5.D, R132.2, T10.1
unnamed: D21.1, R131.1
unnamed: D22.1, R132.1
unnamed: D35.1, R137.1
unnamed: D24.1, R134.1
unnamed: D34.1, R136.1
unnamed: D23.2, D27.1, K1.9, Q6.D
unnamed: D30.1, D34.2, K3.9, Q11.D
unnamed: D33.1, R135.1
unnamed: D29.2, Q8.2, Q9.D, R135.2, T11.1
unnamed: D36.1, R138.1
unnamed: D32.2, Q10.2, Q13.D, R138.2, T12.1
unnamed: D23.1, R133.1
unnamed: D31.1, D35.2, K4.9, Q12.D
unnamed: D25.2, Q2.2, Q3.D, R131.2, T9.1
unnamed: D24.2, D28.1, K2.9, Q7.D
unnamed: Q8.1, TH6.1
unnamed: Q4.1, TH5.1
unnamed: Q2.1, TH4.1
unnamed: J13.2, TH4.2
unnamed: J13.1, TH3.1
unnamed: J15.2, TH7.2
unnamed: J15.1, TH6.2
unnamed: Q10.1, TH7.1
unnamed: J10.1, TH2.2
unnamed: GS7.2, J10.3
unnamed: GS8.2, J11.2
unnamed: GS9.2, J12.2
unnamed: GS10.2, J14.1

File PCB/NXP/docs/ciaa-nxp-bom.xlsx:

Componente | Cantidad | Referencia | Descripción | Modelo de Ejemplo | Link
CR2032_HOLDER | 1 | BT1 | Soporte batería CR2032 | BK-913 | http://www.digikey.com/product-detail/es/BK-913/BK-913-ND/2329371
15p | 2 | C79 C81 | Cap. Cerámico SMD 0603
18pF | 4 | C11 C12 C13 C14 | Cap. Cerámico SMD 0603
20p | 2 | C82 C83 | Cap. Cerámico SMD 0603
22p | 2 | C84 C85 | Cap. Cerámico SMD 0603
470pF | 4 | C38 C40 C44 C92 | Cap. Cerámico SMD 0603
1nF | 4 | C36 C42 C91 C93 | Cap. Cerámico SMD 0603
100nF | 60 | C2 C3 C4 C6 C7 C8 C9 C10 C15 C20 C22 C23 C24 C25 C26 C27 C29 C30 C32 C33 C35 C3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 | Cap. Cerámico SMD 0603
1uF | 1 | C19 | Cap. Cerámico SMD 0603
3.3uF | 1 | C80 | Cap. Cerámico SMD 0603
4.7uF | 3 | C31 C68 C78 | Cap. Elect. Alum. SMD 4mm diám. | UWP1C4R7MCL1GB | http://www.digikey.com/product-detail/es/UWP1C4R7MCL1GB/493-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
10uF | 5 | C1 C5 C18 C34 C60 | Cap. Elect. Alum. SMD 4mm diám.
10uF / 6V3 | 2 | C21 C28 | Cap. Elect. Alum. SMD 4mm diám.
330uF | 1 | C17 | Cap. Elect. Alum. SMD 6.3mm diám.
470uF | 1 | C16 | Cap. Elect. Alum. SMD 12.5mm diám.
BAV199 | 4 | D9 D10 D11 D12 | Diodo dual SOT23
PMEG3020EH | 1 | D1 | Diodo Schottky SOD123F
RS3J-E3/57T | 1 | D2 | Diodo 600V 3A DO214AB
B540C-13-F | 1 | D3 | Reemplazo 1N5825 SMD DO-214AB
LED red | 1 | D4 | LED SMD 0603
LED green | 1 | D5 | LED SMD 0603
PSD12C | 3 | D6 D7 D8 | TVS |  | http://www.protekdevices.com/Assets/Documents/Datasheets/psd.pdf
LL4148 | 12 | D17 D18 D19 D20 D21 D22 D23 D24 D27 D28 D30 D31 | Diodo SOD80
BZX585-B6V8 | 4 | D25 D26 D29 D32 | Zener 6V8 SOD523
MMZ1608B601C | 9 | FB1 FB2 FB3 FB4 FB5 FB6 FB8 FB9 FB10 | EMI Filter 0603
PS2801-4 | 2 | IC1 IC2 | Optoacoplador SMD |  | http://ar.mouser.com/Search/ProductDetail.aspx?R=551-PS2801-4-A
101-00303-68 | 1 | J1 | microSD holder |  | http://ar.mouser.com/ProductDetail/Amphenol-Commercial-Produ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
TB_1X3 | 2 | J2 J4 | Bornera 1x3, paso 2.5mm | Ver Phoenix Contact | http://ar.mouser.com/ProductDetail/Phoenix-Contact/1881451/?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
DB9 | 1 | J3 | Conector D-Sub 9 SMD |  | http://ar.mouser.com/ProductDetail/Kycon/K202XHT-E9S-N/?qs=s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
ZX62-AB-5PA | 2 | J6 P16 | Conector USB SMD |  | http://ar.mouser.com/search/ProductDetail.aspx?qs=XQjbzJWzFP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
USB_microB | 1 | J7
JUMPER | 14 | JP1 JP2 JP3 JP4 JP5 JP6 JP7 JP9 JP11 JP13 JP8 JP10 JP12 JP14 | Tira de pines 2.54mm pitch con jumper
G5V-2-DC5 | 4 | K1 K2 K3 K4 | Relé Low Signal (alternativo: C93401)
47uH | 1 | L2 | Inductor 3A SMD B82477G4473M3 |  | http://ar.mouser.com/ProductDetail/EPCOS/B82477G4473M3/?qs=s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
BK1608HS220-T | 1 | L1 | Inductor SMD 0603
HR911105A | 1 | P1 | Conector Ethernet con trafos integrados |  | http://ar.mouser.com/ProductDetail/Pulse/J0011D01BNL/?qs=%2f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
PWR | 1 | P2 | Bornera 1x2, paso 2.5mm | Ver Phoenix Contact
Analog1 | 1 | P3 | Bornera 1x2, paso 2.5mm | Ver Phoenix Contact
Analog2 | 1 | P4 | Bornera 1x2, paso 2.5mm | Ver Phoenix Contact
Analog3 | 1 | P5 | Bornera 1x2, paso 2.5mm | Ver Phoenix Contact
Analog4 | 1 | P6 | Bornera 1x2, paso 2.5mm | Ver Phoenix Contact
Entradas Digitales | 1 | P7 | Bornera 1x9, paso 2.5mm | Ver Phoenix Contact
Cortex-Debug | 1 | P8 | Conector 10 pines SMD 1.27mm |  | http://www.samtec.com/documents/webfiles/cpdf/FTSH-1XX-XX-XX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
CONN_5X2 | 1 | P10 | Bornera 1x10, paso 2.5mm | Ver Phoenix Contact
RELES | 1 | P11 | Bornera 2x13, paso 2.5mm | Ver Phoenix Contact
USMF020 | 2 | PS1 PS2 | Polyswitch
IRF820S | 4 | Q2 Q4 Q8 Q10 | MOSFET-N de potencia SMD
BSS209PW | 1 | Q1 | MOSFET-P SOT-323
NDS7002A | 8 | Q3 Q5 Q6 Q7 Q9 Q11 Q12 Q13 | MOSFET-N SMD SOT-23
0 | 13 | R7 R8 R9 R13 R14 R80 R81 R82 R83 R86 R87 R88 R89 | SMD 0603
4.7 | 4 | R53 R61 R123 R128 | SMD 0603
22 | 3 | R10 R11 R12 | SMD 0603
24.9 | 1 | R20 | SMD 0603
50 | 4 | R3 R4 R5 R6 | SMD 0603
60 | 2 | R43 R46 | SMD 0603
100 | 12 | R65 R67 R69 R71 R73 R75 R77 R79 R51 R54 R57 R60 | SMD 0603
120 | 1 | R35 | SMD 0603
237 | 4 | R55 R62 R124 R129 | 0.1% 25ppm/°C SMD 0603
270 | 2 | R17 R18 | SMD 0603
270R | 1 | R44 | SMD 0603
330 | 1 | R84 | SMD 0603
680 | 3 | R24 R32 R39 | SMD 0603
1k | 2 | R22 R98 | SMD 0603
1K5 | 3 | R1 R42 R45 | SMD 0603
2.2k | 3 | R99 R100 R104 | SMD 0603
3.3k | 4 | R105 R107 R109 R113 | SMD 0603
4K7 | 5 | R34 R36 R37 R41 R47 | SMD 0603
10k | 32 | R2 R15 R16 R23 R25 R26 R27 R28 R29 R30 R31 R48 R49 R64 R66 R68 R70 R72 R74 R76 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 | SMD 0603
12K 1% | 3 | R95 R19 R97 | SMD 0603
15k | 14 | R50 R52 R56 R58 R59 R63 R121 R122 R125 R126 R127 R130 R93 R94 | 0.1% 25ppm/°C SMD 0603
100k | 11 | R21 R106 R108 R110 R111 R112 R114 R115 R116 R33 R38 | SMD 0603
10M | 1 | R96 | SMD 0603
100 / 1/2W | 1 | R40 | SMD 1206
SW_PUSH | 1 | SW1 | Tact switch SPST
NSI50010YT1G | 8 | T1 T2 T3 T4 T5 T6 T7 T8 | Current limiter
PTS18126V300 | 1 | TH1 | Polyswitch 3A SMD
PTS12066V100 | 6 | TH2 TH3 TH4 TH5 TH6 TH7 | Polyswitch 1A SMD
MF-MSMF030-2 | 2 | TH8 TH9 | Polyswitch 0.3A SMD
LAN8720A-CP | 1 | U1 | Ethernet PHY
ST3232E | 1 | U6 | Transceiver RS232 16-TSSOP
TJA1040 | 1 | U7 | Transceiver CAN 8-SOIC
PESD1CAN | 1 | U8 | TVS para CAN
MIC2025-2YM | 1 | U10 | Switch USB 8-TSSOP
MCP6024 | 1 | U11 | OpAmp 14-TSSOP
24AA1025 | 1 | U13 | EEPROM 128kB
TXB0108 | 1 | U14 | Buffer bidireccional 20-TSSOP
IS42S16400F | 1 | U15 | SDRAM 64Mb 54-TSOP
FT2232H | 1 | U17 | USB IC 64-LQFP
NCP1117ST33T3G | 2 | U18 U4 | Regulador 3.3V SOT223
AT93C46D | 1 | U19 | EEPROM 8-TSSOP, MicroWire
MAX3072 | 1 | U5 | Transceiver RS485 8-SOIC
SI502 | 1 | U2 | Oscilador 50MHz SMD
LM2596SX-5.0/NOPB | 1 | U3 | Regulador 5V TO263-5
PRTR5V0U2X | 1 | U9 | TVS para USB
LPC4337JBD144 | 1 | U16 | Microcontrolador
32.768K | 1 | X1 | Cristal SMD
12MHz | 2 | X2 X3 | Cristal SMD
SMBJ20CA | 4 | ZA2 ZA3 ZA4 ZA5 | TVS SMD
SMP30A | 1 | ZA1 | TVS SMD
P6SMB33CA | 8 | ZA6 ZA7 ZA8 ZA9 ZA10 ZA11 ZA12 ZA13 | TVS SMD
SMAZ5V6 | 1 | ZA14 | Zener SMD
